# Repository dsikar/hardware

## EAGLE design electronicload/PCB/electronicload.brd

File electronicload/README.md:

# Electronic Load

## Revision 1

From http://jasper.sikken.nl/electronicload/index.html

## BOM
```
Custom designed PCB ($23)
Arduino Nano board ($12)
2x 15pins 0.1" pitch female header connectors ($2)
AD8608 Rail-to-rail opamps ($3)
MCP4725 DAC ($3)
IRLZ44Z N-channel MOSFET ($2)
SK 129 38mm Heat sink ($1)
0603 resistors and capacitors ($2)
screw terminal ($1)
```

## Board errata

Missing rails::

## Revision 2

Hardware: https://github.com/jrsikken/ElectronicLoadR2  
Software: https://github.com/bertrik/ElectronicLoadR2

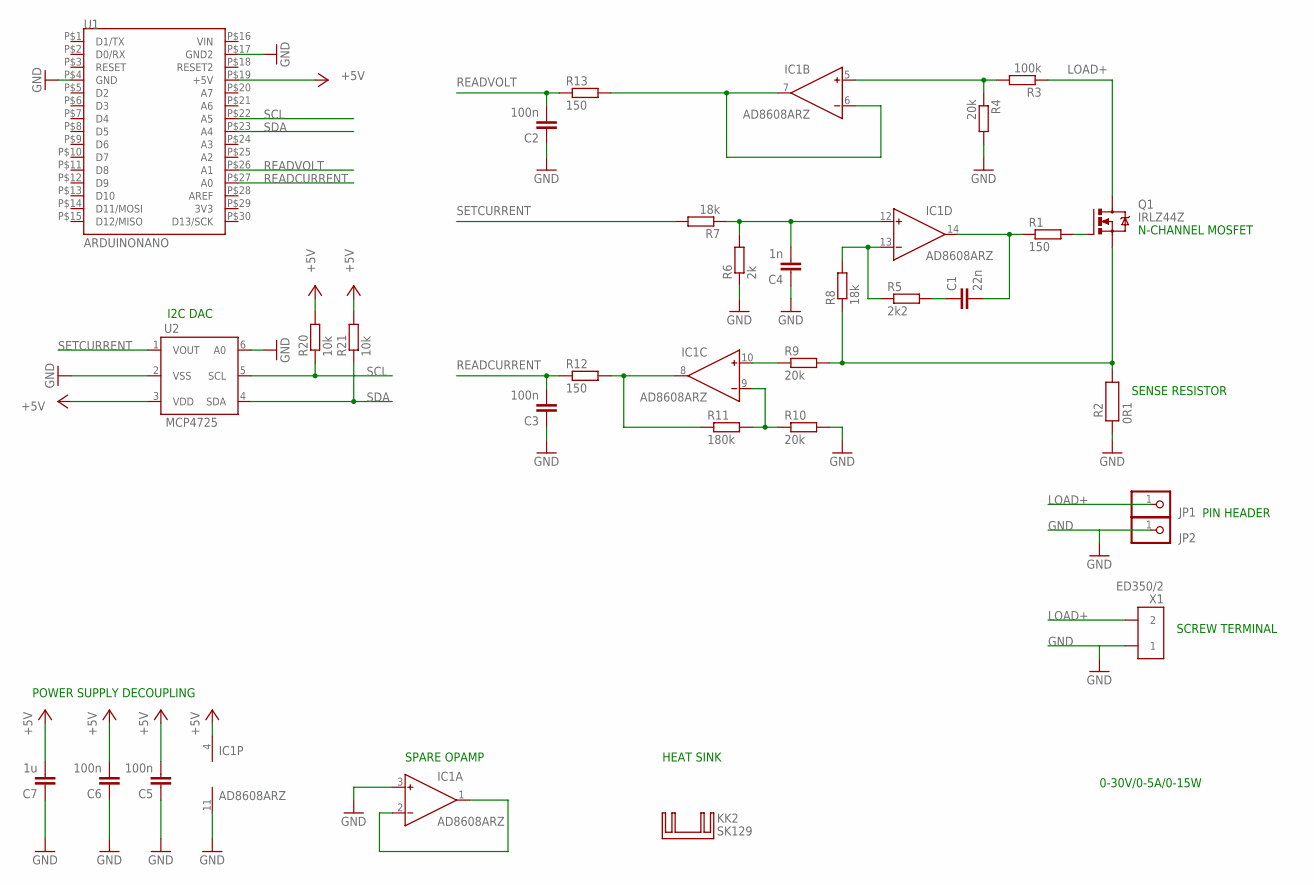
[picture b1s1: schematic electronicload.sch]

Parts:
C1: 22n; C0603K; TOLERANCE 10%; VOLTAGE 25V; DIGIKEY 445-12490-1-ND
C2, C3, C5, C6: 100n; C0603K; TOLERANCE 10%; VOLTAGE 50V; DIGIKEY 445-7456-1-ND
C4: 1n; C0603K; TOLERANCE 10%; VOLTAGE 50V; DIGIKEY 445-12511-1-ND
C7: 1u; C0603K; TOLERANCE 10%; VOLTAGE 16V; DIGIKEY 311-1444-1-ND
IC1: AD8608ARZ; SO14
JP1, JP2: PINHD-1X1; 1X01
KK2: SK129; SK129-HOLE
Q1: IRLZ44Z; TO220BV
R1, R12, R13: 150; R0603; DIGIKEY RMCF0603JT150RCT-ND
R2: 0R1; S3
R3: 100k; R0603; DIGIKEY RMCF0603JT100KCT-ND
R4, R9, R10: 20k; R0603; DIGIKEY RMCF0603JT20K0CT-ND
R5: 2k2; R0603; DIGIKEY RMCF0603JT2K20CT-ND
R6: 2k; R0603; DIGIKEY RMCF0603JT2K00CT-ND
R7, R8: 18k; R0603; DIGIKEY RMCF0603JT18K0CT-ND
R11: 180k; R0603; DIGIKEY RMCF0603JT180KCT-ND
R20, R21: 10k; R0603; DIGIKEY RMCF0603JT10K0CT-ND
U1: ARDUINONANO
U2: MCP4725; SOT-23-6
X1: ED350/2

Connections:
+5V: C5.2, C6.2, C7.2, IC1.4 (V+), R20.2, R21.2, U1.P$19 (+5V), U2.3 (VDD)
GATE: Q1.G, R1.2
GND: C2.1, C3.1, C4.1, C5.1, C6.1, C7.1, IC1.3 (IN+), IC1.11 (V-), JP2.1, R2.1, R4.2, R6.1, R10.2, U1.P$4 (GND), U1.P$17 (GND2), U2.2 (VSS), U2.6 (A0), X1.P$1 (1)
LOAD+: JP1.1, Q1.D, R3.1, X1.P$2 (2)
unnamed: C1.2, IC1.14 (OUT), R1.1
unnamed: IC1.6 (IN-), IC1.7 (OUT), R13.2
unnamed: IC1.10 (IN+), R9.1
unnamed: IC1.13 (IN-), R5.1, R8.2
unnamed: IC1.5 (IN+), R3.2, R4.1
unnamed: C4.2, IC1.12 (IN+), R6.2, R7.1
unnamed: IC1.9 (IN-), R10.1, R11.2
unnamed: IC1.8 (OUT), R11.1, R12.2
unnamed: C1.1, R5.2
unnamed: IC1.1 (OUT), IC1.2 (IN-)
READCURRENT: C3.2, R12.1, U1.P$27 (A0)
READVOLT: C2.2, R13.1, U1.P$26 (A1)
SCL: R20.1, U1.P$22 (A5), U2.5 (SCL)
SDA: R21.1, U1.P$23 (A4), U2.4 (SDA)
SENSE: Q1.S, R2.2, R8.1, R9.2
SETCURRENT: R7.2, U2.1 (VOUT)

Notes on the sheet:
SPARE OPAMP
HEAT SINK
POWER SUPPLY DECOUPLING
PIN HEADER
SCREW TERMINAL
0-30V/0-5A/0-15W
SENSE RESISTOR
N-CHANNEL MOSFET
I2C DAC

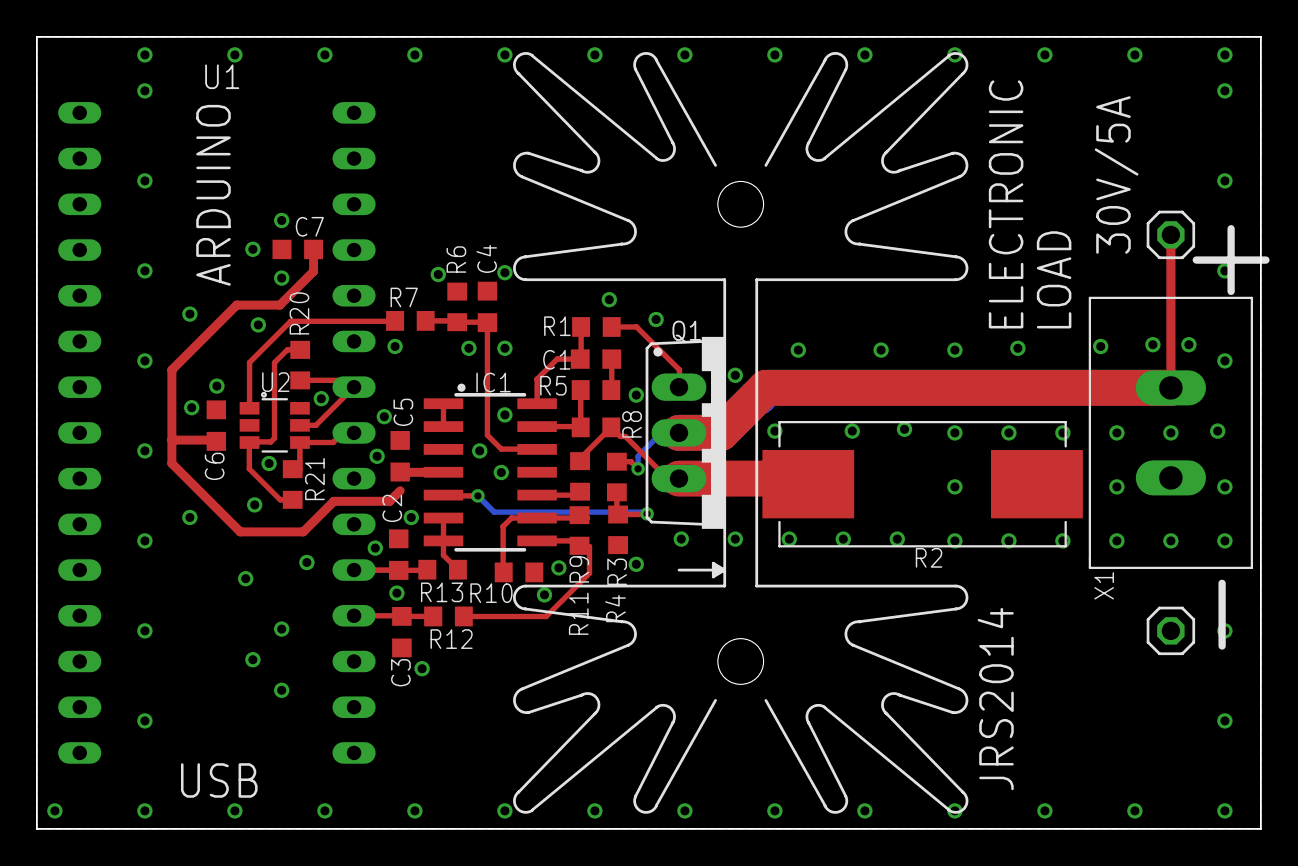
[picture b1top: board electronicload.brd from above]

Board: 2 copper layers, 68.0 x 44.0 mm, 30 parts (0 on the bottom side), 20 nets.

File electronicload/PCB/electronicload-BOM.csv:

Qty,Value,Device,Package,Parts,Description
2,,PINHD-1X1,1X01,JP1 + JP2,PIN HEADER
1,0R1,0R1,S3,R2,S3-0R1F1
1,100k,R-EU_R0603,R0603,R3,RESISTOR + European symbol
4,100n,C-EUC0603K,C0603K,C2 + C3 + C5 + C6,CAPACITOR + European symbol
2,10k,R-EU_R0603,R0603,R20 + R21,RESISTOR + European symbol
3,150,R-EU_R0603,R0603,R1 + R12 + R13,RESISTOR + European symbol
1,180k,R-EU_R0603,R0603,R11,RESISTOR + European symbol
2,18k,R-EU_R0603,R0603,R7 + R8,RESISTOR + European symbol
1,1n,C-EUC0603K,C0603K,C4,CAPACITOR + European symbol
1,1u,C-EUC0603K,C0603K,C7,CAPACITOR + European symbol
3,20k,R-EU_R0603,R0603,R4 + R9 + R10,RESISTOR + European symbol
1,22n,C-EUC0603K,C0603K,C1,CAPACITOR + European symbol
1,2k,R-EU_R0603,R0603,R6,RESISTOR + European symbol
1,2k2,R-EU_R0603,R0603,R5,RESISTOR + European symbol
1,AD8608ARZ,AD8608R,SO14,IC1,Precision + Low Noise + CMOS + Rail-to-Rail + Input/Output Operational Amplifiers
1,ARDUINONANO,ARDUINONANO,ARDUINONANO,U1,
1,ED350/2,ED350/2,ED350/2,X1,ED350/X (5.0 mm) TERMINAL BLOCK 5MM VERT 2POS PCB
1,IRLZ44Z,IRLZ44Z,TO220BV,Q1,N-Channel HEXFET® Power MOSFET Logic Level
1,MCP4725,MCP4725,SOT-23-6,U2,12-Bit Digital-to-Analog Converter with EEPROM Memory
1,SK129,SK129,SK129-HOLE,KK2,HEATSINK manufacturer Fischer/distributor Buerklin

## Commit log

2018-02-05 uCurrent build initial commit.
2018-02-06 Adding UK suppliers.
2018-02-06 Added UK supplier list.
2018-02-06 Made a start on Electronic Load Revision 1 BOM.
2018-02-07 Made a start on Electronic Load BOM.
2018-02-08 Made a start on ElectronicLoad BOM.
2018-02-09 Added eagle files and bom.
2018-02-27 Updated BOM.
2018-03-12 Updated bom pdf.
2018-04-11 Test box initial commit.
2018-04-12 Changed connector to PUD series.
2018-04-17 Added alternative SH series connectors.
2018-04-18 Updated BOM with pre-crimped alternatives.
2018-04-18 Number crunching
2018-04-18 Pricing per assembly
2018-04-24 Added totals
2018-04-27 Updated BOM
2018-05-01 Edits
2018-05-01 Added alternative suppliers.
2018-05-29 Cross-referencing and .csv version
